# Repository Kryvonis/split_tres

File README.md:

# Readme

[Editor](https://nickcoutsos.github.io/keymap-editor/)

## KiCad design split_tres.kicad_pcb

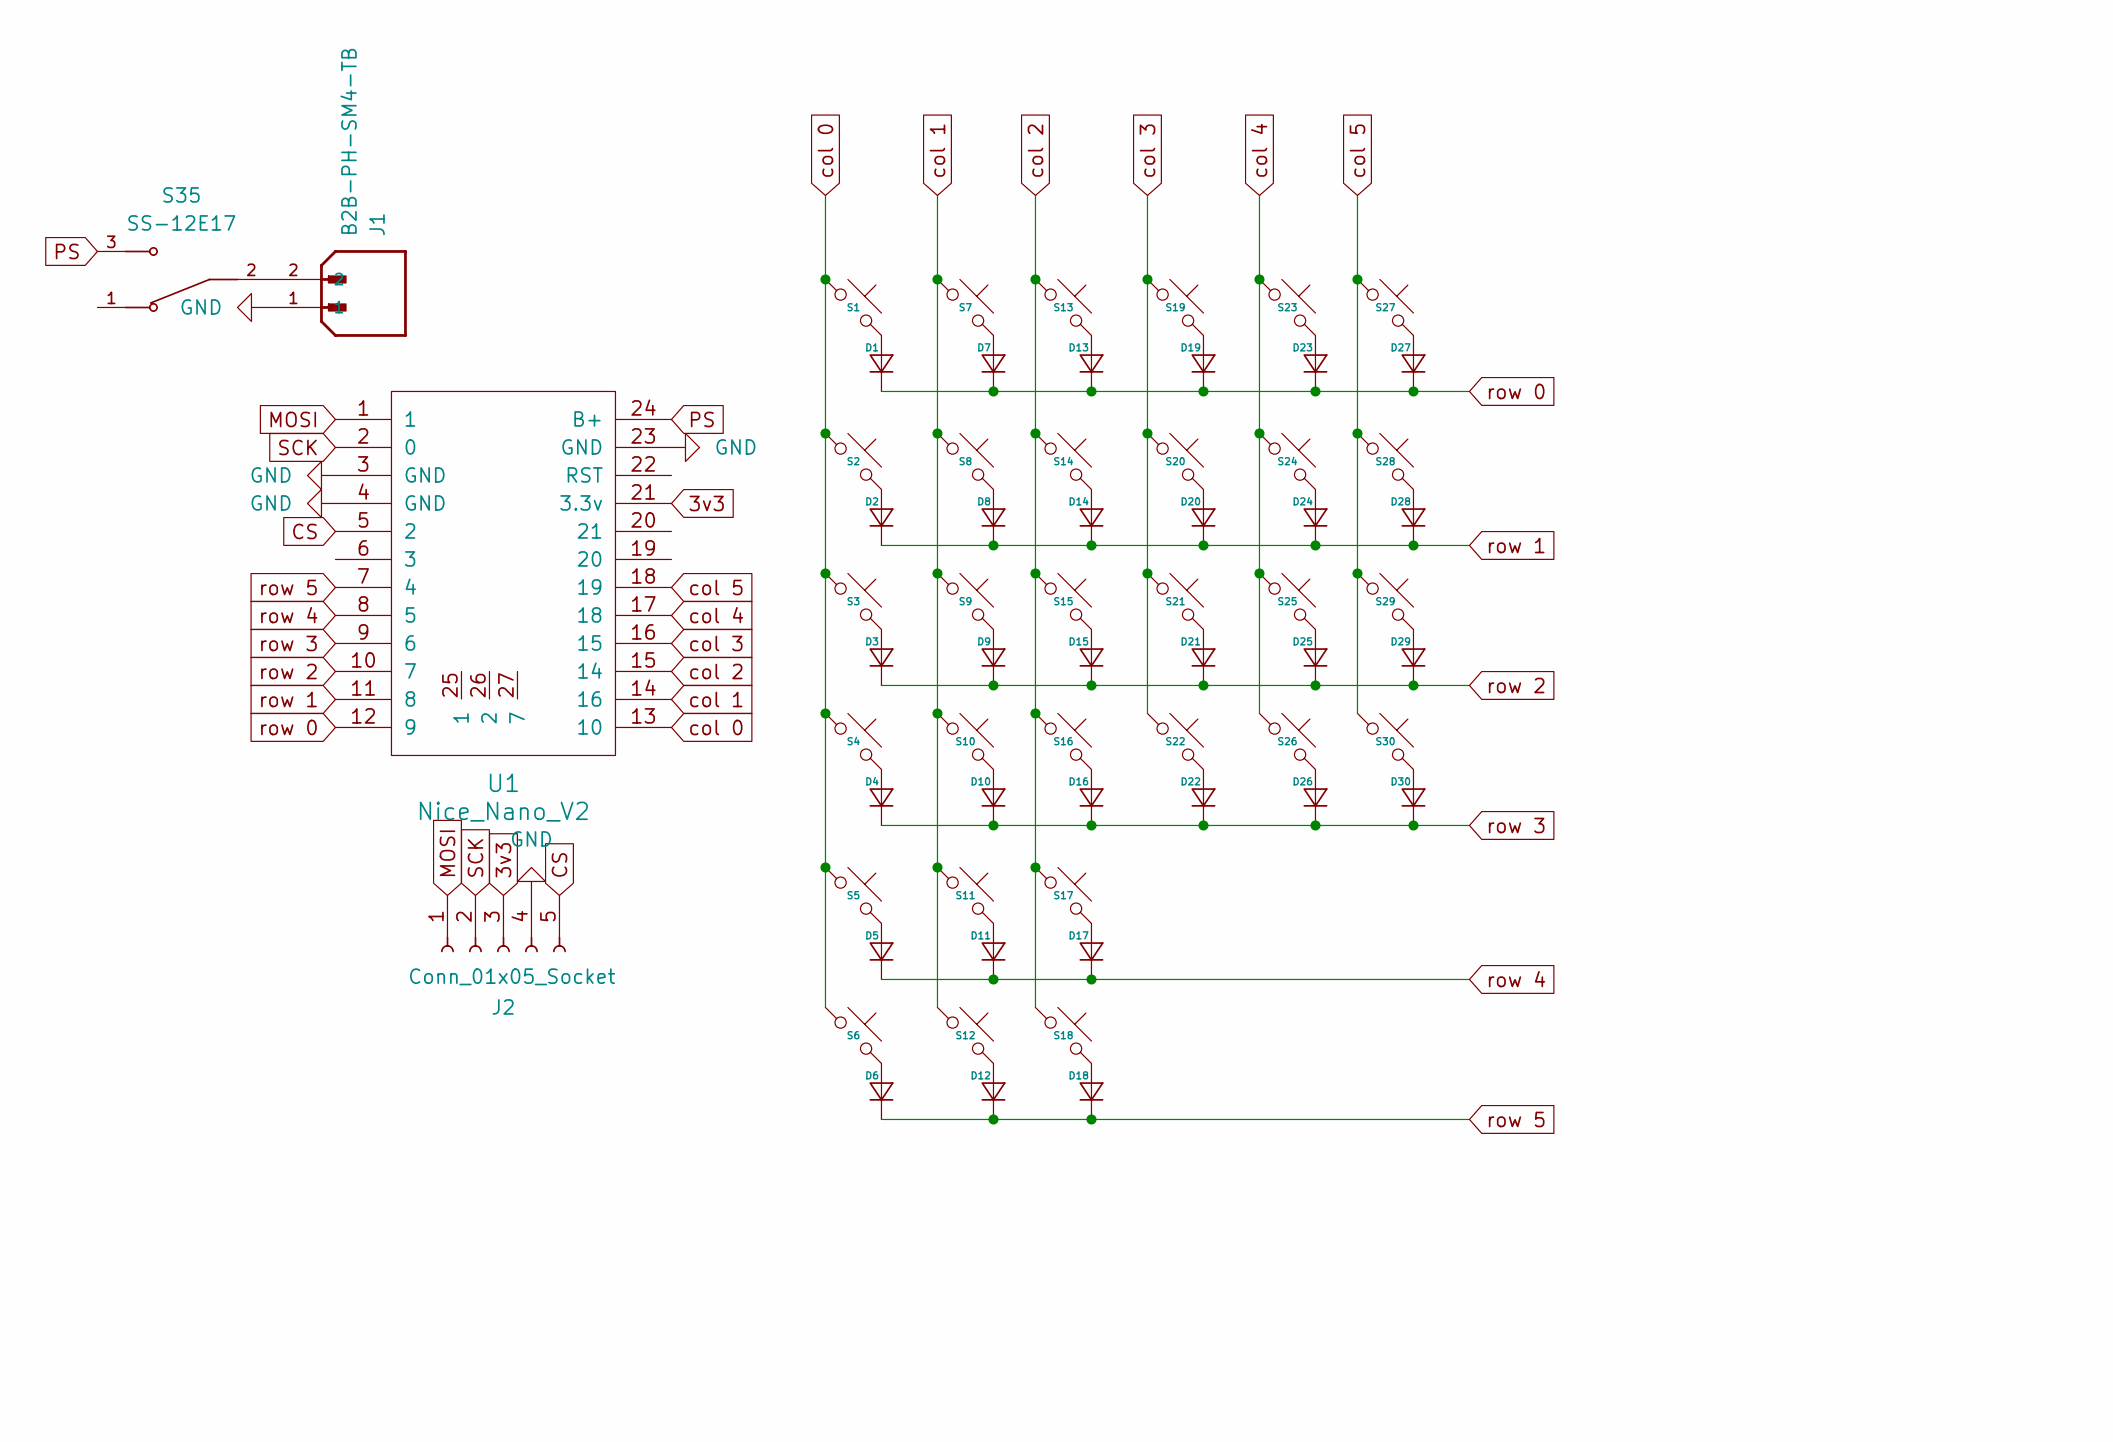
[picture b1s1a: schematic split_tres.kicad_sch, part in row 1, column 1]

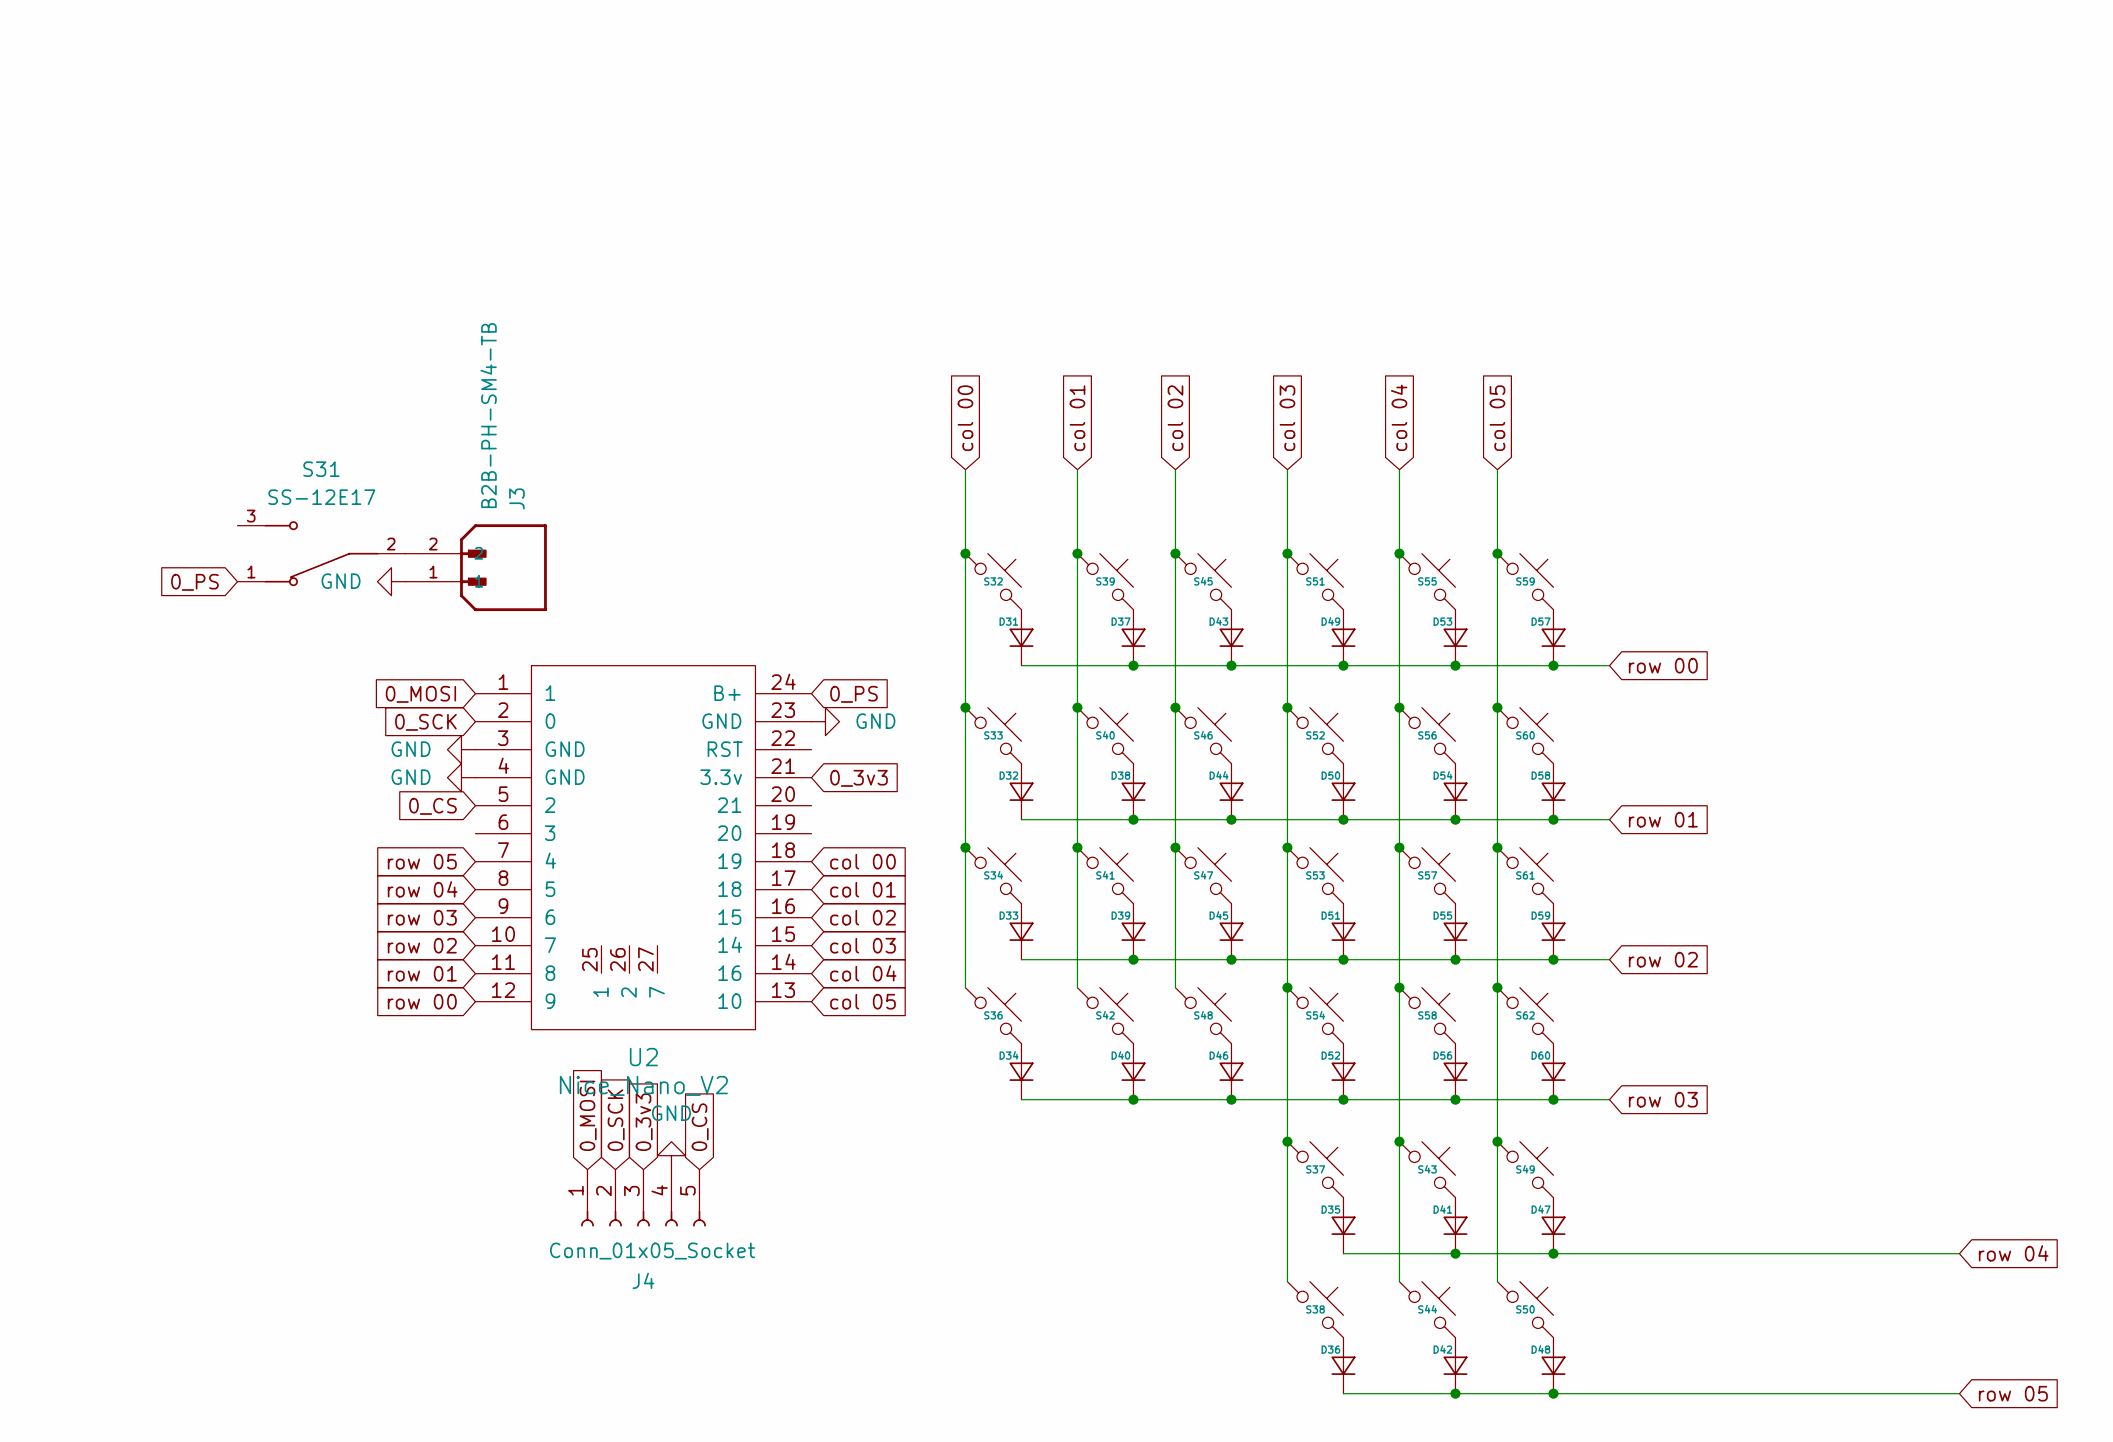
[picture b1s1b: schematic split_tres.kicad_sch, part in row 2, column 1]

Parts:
D1, D2, D3, D4, D5, D6, D7, D8, D9, D10, D11, D12, D13, D14, D15, D16, D17, D18, D19, D20, D21, D22, D23, D24, D25, D26, D27, D28, D29, D30, D31, D32, D33, D34, D35, D36, D37, D38, D39, D40, D41, D42, D43, D44, D45, D46, D47, D48, D49, D50, D51, D52, D53, D54, D55, D56, D57, D58, D59, D60: Diode_DO-35
J1, J3: B2B-PH-SM4-TB; JST_B2B-PH-SM4-TB; PARTREV N/A
J2, J4: Conn_01x05_Socket; PinSocket_1x05_P2.54mm_Vertical
S1, S2, S3, S4, S5, S6, S7, S8, S9, S10, S11, S12, S13, S14, S15, S16, S17, S18, S19, S20, S21, S22, S23, S24, S25, S26, S27, S28, S29, S30, S32, S33, S34, S36, S37, S38, S39, S40, S41, S42, S43, S44, S45, S46, S47, S48, S49, S50, S51, S52, S53, S54, S55, S56, S57, S58, S59, S60, S61, S62: Choc_V2
S31, S35: SS-12E17; SW_SS-12E17; PARTREV N/A
U1, U2: Nice_Nano_V2

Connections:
0_3v3: J4.3, U2.21 (3.3v)
0_CS: J4.5, U2.5 (2)
0_MOSI: J4.1, U2.1
0_PS: S31.1, S31.3, U2.24 (B+)
0_SCK: J4.2, U2.2 (0)
3v3: J2.3, U1.21 (3.3v)
CS: J2.5, U1.5 (2)
GND: J1.1, J2.4, J3.1, J4.4, U1.3 (GND), U1.4 (GND), U1.23 (GND), U2.3 (GND), U2.4 (GND), U2.23 (GND)
MOSI: J2.1, U1.1
unnamed: D1.2 (A), S1.2
unnamed: D2.2 (A), S2.2
unnamed: D3.2 (A), S3.2
unnamed: D4.2 (A), S4.2
unnamed: D5.2 (A), S5.2
unnamed: D6.2 (A), S6.2
unnamed: D7.2 (A), S7.2
unnamed: D8.2 (A), S8.2
unnamed: D9.2 (A), S9.2
unnamed: D10.2 (A), S10.2
unnamed: D11.2 (A), S11.2
unnamed: D12.2 (A), S12.2
unnamed: D13.2 (A), S13.2
unnamed: D14.2 (A), S14.2
unnamed: D15.2 (A), S15.2
unnamed: D16.2 (A), S16.2
unnamed: D17.2 (A), S17.2
unnamed: D18.2 (A), S18.2
unnamed: D19.2 (A), S19.2
unnamed: D20.2 (A), S20.2
unnamed: D21.2 (A), S21.2
unnamed: D22.2 (A), S22.2
unnamed: D23.2 (A), S23.2
unnamed: D24.2 (A), S24.2
unnamed: D25.2 (A), S25.2
unnamed: D26.2 (A), S26.2
unnamed: D27.2 (A), S27.2
unnamed: D28.2 (A), S28.2
unnamed: D29.2 (A), S29.2
unnamed: D30.2 (A), S30.2
unnamed: D31.2 (A), S32.2
unnamed: D32.2 (A), S33.2
unnamed: D33.2 (A), S34.2
unnamed: D34.2 (A), S36.2
unnamed: D35.2 (A), S37.2
unnamed: D36.2 (A), S38.2
unnamed: D37.2 (A), S39.2
unnamed: D38.2 (A), S40.2
unnamed: D39.2 (A), S41.2
unnamed: D40.2 (A), S42.2
unnamed: D41.2 (A), S43.2
unnamed: D42.2 (A), S44.2
unnamed: D43.2 (A), S45.2
unnamed: D44.2 (A), S46.2
unnamed: D45.2 (A), S47.2
unnamed: D46.2 (A), S48.2
unnamed: D47.2 (A), S49.2
unnamed: D48.2 (A), S50.2
unnamed: D49.2 (A), S51.2
unnamed: D50.2 (A), S52.2
unnamed: D51.2 (A), S53.2
unnamed: D52.2 (A), S54.2
unnamed: D53.2 (A), S55.2
unnamed: D54.2 (A), S56.2
unnamed: D55.2 (A), S57.2
unnamed: D56.2 (A), S58.2
unnamed: D57.2 (A), S59.2
unnamed: D58.2 (A), S60.2
unnamed: D59.2 (A), S61.2
unnamed: D60.2 (A), S62.2
unnamed: J1.2, S35.2
unnamed: J3.2, S31.2
PS: S35.3, U1.24 (B+)
SCK: J2.2, U1.2 (0)
col 00: S32.1, S33.1, S34.1, S36.1, U2.18 (19)
col 0: S1.1, S2.1, S3.1, S4.1, S5.1, S6.1, U1.13 (10)
col 01: S39.1, S40.1, S41.1, S42.1, U2.17 (18)
col 1: S7.1, S8.1, S9.1, S10.1, S11.1, S12.1, U1.14 (16)
col 2: S13.1, S14.1, S15.1, S16.1, S17.1, S18.1, U1.15 (14)
col 02: S45.1, S46.1, S47.1, S48.1, U2.16 (15)
col 03: S37.1, S38.1, S51.1, S52.1, S53.1, S54.1, U2.15 (14)
col 3: S19.1, S20.1, S21.1, S22.1, U1.16 (15)
col 4: S23.1, S24.1, S25.1, S26.1, U1.17 (18)
col 04: S43.1, S44.1, S55.1, S56.1, S57.1, S58.1, U2.14 (16)
col 5: S27.1, S28.1, S29.1, S30.1, U1.18 (19)
col 05: S49.1, S50.1, S59.1, S60.1, S61.1, S62.1, U2.13 (10)
row 00: D31.1 (K), D37.1 (K), D43.1 (K), D49.1 (K), D53.1 (K), D57.1 (K), U2.12 (9)
row 0: D1.1 (K), D7.1 (K), D13.1 (K), D19.1 (K), D23.1 (K), D27.1 (K), U1.12 (9)
row 01: D32.1 (K), D38.1 (K), D44.1 (K), D50.1 (K), D54.1 (K), D58.1 (K), U2.11 (8)
row 1: D2.1 (K), D8.1 (K), D14.1 (K), D20.1 (K), D24.1 (K), D28.1 (K), U1.11 (8)
row 02: D33.1 (K), D39.1 (K), D45.1 (K), D51.1 (K), D55.1 (K), D59.1 (K), U2.10 (7)
row 2: D3.1 (K), D9.1 (K), D15.1 (K), D21.1 (K), D25.1 (K), D29.1 (K), U1.10 (7)
row 03: D34.1 (K), D40.1 (K), D46.1 (K), D52.1 (K), D56.1 (K), D60.1 (K), U2.9 (6)
row 3: D4.1 (K), D10.1 (K), D16.1 (K), D22.1 (K), D26.1 (K), D30.1 (K), U1.9 (6)
row 04: D35.1 (K), D41.1 (K), D47.1 (K), U2.8 (5)
row 4: D5.1 (K), D11.1 (K), D17.1 (K), U1.8 (5)
row 05: D36.1 (K), D42.1 (K), D48.1 (K), U2.7 (4)
row 5: D6.1 (K), D12.1 (K), D18.1 (K), U1.7 (4)

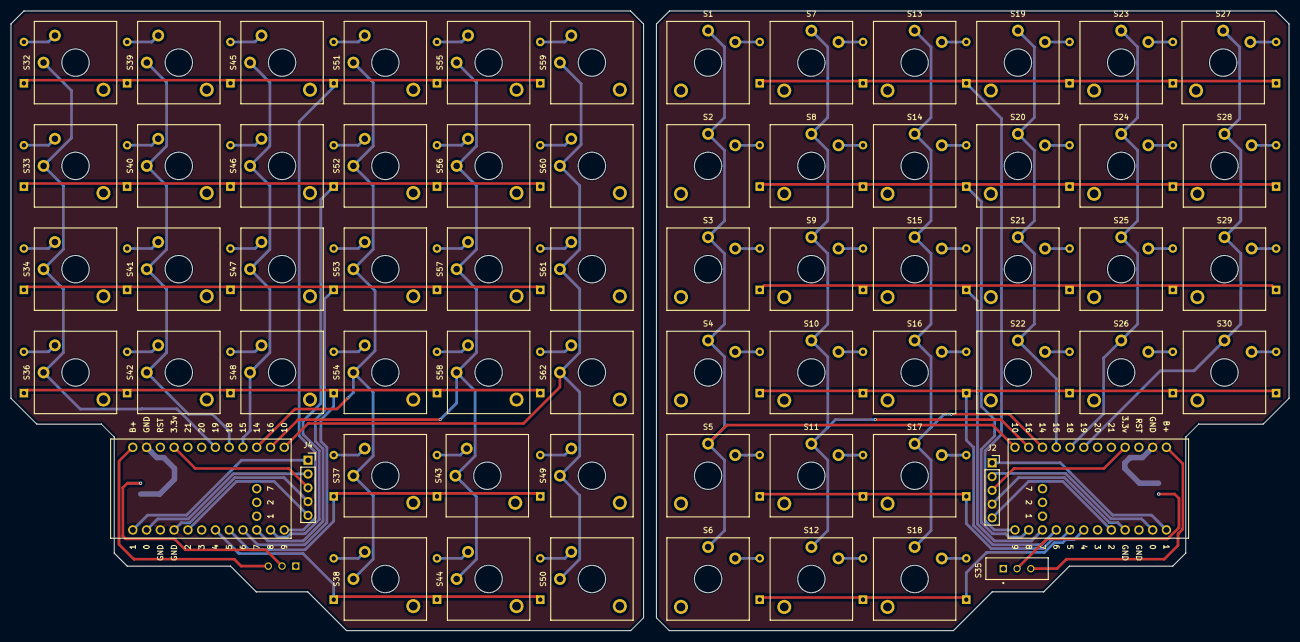
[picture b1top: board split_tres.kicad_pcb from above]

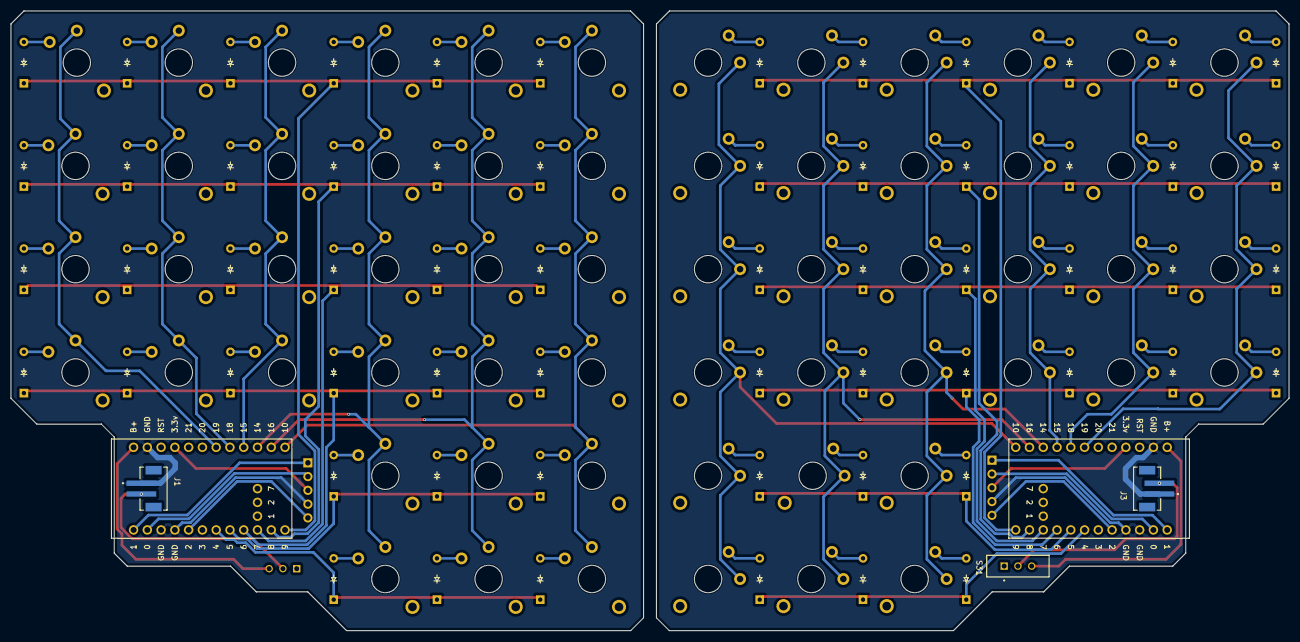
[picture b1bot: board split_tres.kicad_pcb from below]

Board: 2 copper layers, 235.7 x 114.3 mm, 128 parts (64 on the bottom side), 97 nets.

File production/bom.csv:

Designator,Footprint,Quantity,Value,LCSC Part #
"D1, D10, D11, D12, D13, D14, D15, D16, D17, D18, D19, D2, D20, D21, D22, D23, D24, D25, D26, D27, D28, D29, D3, D30, D31, D32, D33, D34, D35, D36, D37, D38, D39, D4, D40, D41, D42, D43, D44, D45, D46, D47, D48, D49, D5, D50, D51, D52, D53, D54, D55, D56, D57, D58, D59, D6, D60, D7, D8, D9",Diode_DO-35,60,~,
"J1, J3",JST_B2B-PH-SM4-TB,2,B2B-PH-SM4-TB,
"J2, J4",PinSocket_1x05_P2.54mm_Vertical,2,Conn_01x05_Socket,
"S1, S10, S11, S12, S13, S14, S15, S16, S17, S18, S19, S2, S20, S21, S22, S23, S24, S25, S26, S27, S28, S29, S3, S30, S32, S33, S34, S36, S37, S38, S39, S4, S40, S41, S42, S43, S44, S45, S46, S47, S48, S49, S5, S50, S51, S52, S53, S54, S55, S56, S57, S58, S59, S6, S60, S61, S62, S7, S8, S9",Choc_V2,60,~,
"S31, S35",SW_SS-12E17,2,SS-12E17,
"U1, U2",Nice_Nano_V2,2,Nice_Nano_V2,

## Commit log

2026-04-14 init
2026-04-14 rename
2026-04-14 nice view
2026-04-14 build
2026-04-14 update system
2026-04-14 version
2026-04-15 move
2026-04-15 Move boards directory and update to ZMK main
2026-04-15 layout
2026-04-15 view
2026-04-15 setup
2026-04-15 new module
2026-04-20 feat: expand ZMK board support, enhance testing framework, and update ZMK Studio documentation and infrastructure
2026-04-20 miso
2026-05-11 squad
2026-05-11 uart disable
2026-05-11 no panic
2026-05-11 left view
2026-05-11 splitsquad
2026-05-11 lint
2026-05-22 keymap
2026-05-22 studio
2026-05-23 r schema
